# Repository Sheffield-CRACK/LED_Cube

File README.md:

# Trackellite
Software for desktop satellite tracking toy. 
Will query for TLE files daily, and produce a grid of how many satellites are where in real time. This uses an arduino and a series of SIPO shift registers to drive the actual cube. The python script `send_cube.py` contains a function, `conv2byte_vect`, which converts a numpy array (or list) to something that can be transmitted to the arduino. Something like this:

```python
# Start the serial connection
ser = serial.Serial('/dev/cu.wchusbserial72', 9600, timeout=.1)
print("Waiting for Arduino to start...")
time.sleep(2)
print("\n\n\nReady to start transmitting!")

# Bouncing Box
di = 1
i = 1
while True:
    if i == 6 or i == 0:
        di = -di
    i += di

    temp_data = np.array(data, copy=True)
    temp_data[i:i+2, i:i+2, i:i+2] = 1

    writeable_data = conv2byte_vect(temp_data)
    ser.write(writeable_data)

    time.sleep(0.1)

ser.close()
```

## TLE, and the basics of the Raspberry Pi's job
This is how satellite/orbital junk ephemerides are reported. It's basically just the position of the thing at two moments in time, then you extrapolate out from there. I'm using ported NASA code to do this - if it's good enough for NASA it's good enough for me, and I cant be arsed to write the code for that. They're somehow still using a system built to work with punchcards? Fortran users must feel vindicated.

Once a day, the full list of TLE files from [here](https://celestrak.com/NORAD/elements/) is downloaded, and each is checked to see if it passes overhead to the user. If it does, the pi puts it in its pocket, but if it doesn't it gets chucked away. Then, the pi starts constantly checking what's overhead and generating a grid, with the number of objects in each cell. The grid corresponds to the volume of space above the user. The plan is to then use this to light up the grid, corresponding to how the space junk is positioned above the user.

# Checklist:
- [DONE] [SLOW, DONT USE] Query N2YO for satellites
- [DONE] Compute my own satellite locations
- [DONE] Figure out how to plug the grid into LED matrix
  - LED matrix, c.f. [here](https://www.instructables.com/id/Led-Cube-8x8x8/)?
- [DONE] Get the software running on a raspberry pi (3B+? or will a zero work?)
- Breadboard a prototype LED matrix [DONE] and control it [TODO]
  - This needs to be done differently. I was going to do it straight off the pi, but thinking about it, it'd be better to have one (or several) arudinos handle the LEDs, so that the pi can focus on the satellites. An arduino MEGA has like, 56 GPIO pins or something, so one of those could easily handle a 4x5x5 grid (4 + 25 pins needed). Slap some transistors on that and we'd be good to go I think, though I'd probably want a breadboard hat for the arduino, vs *learning how to make a PCB(!!)* and getting that manufactured. And there's no way I'm doing this with loose wires.
- [DONE] Wire together a 3D grid of LEDs
  - I bought some stainless steel wire to use as conductor and scaffold - but solder doesn't stick to it >:(
  - I need something else. Bare steel wire maybe? Or use the scaffold and wrap a current carrier around it? [This worked]
- [DONE] Control the cube from python, through the arduino driver.
- [lol] Make a nice case
- Add a screen? Links to satellites on web trackers for more info?

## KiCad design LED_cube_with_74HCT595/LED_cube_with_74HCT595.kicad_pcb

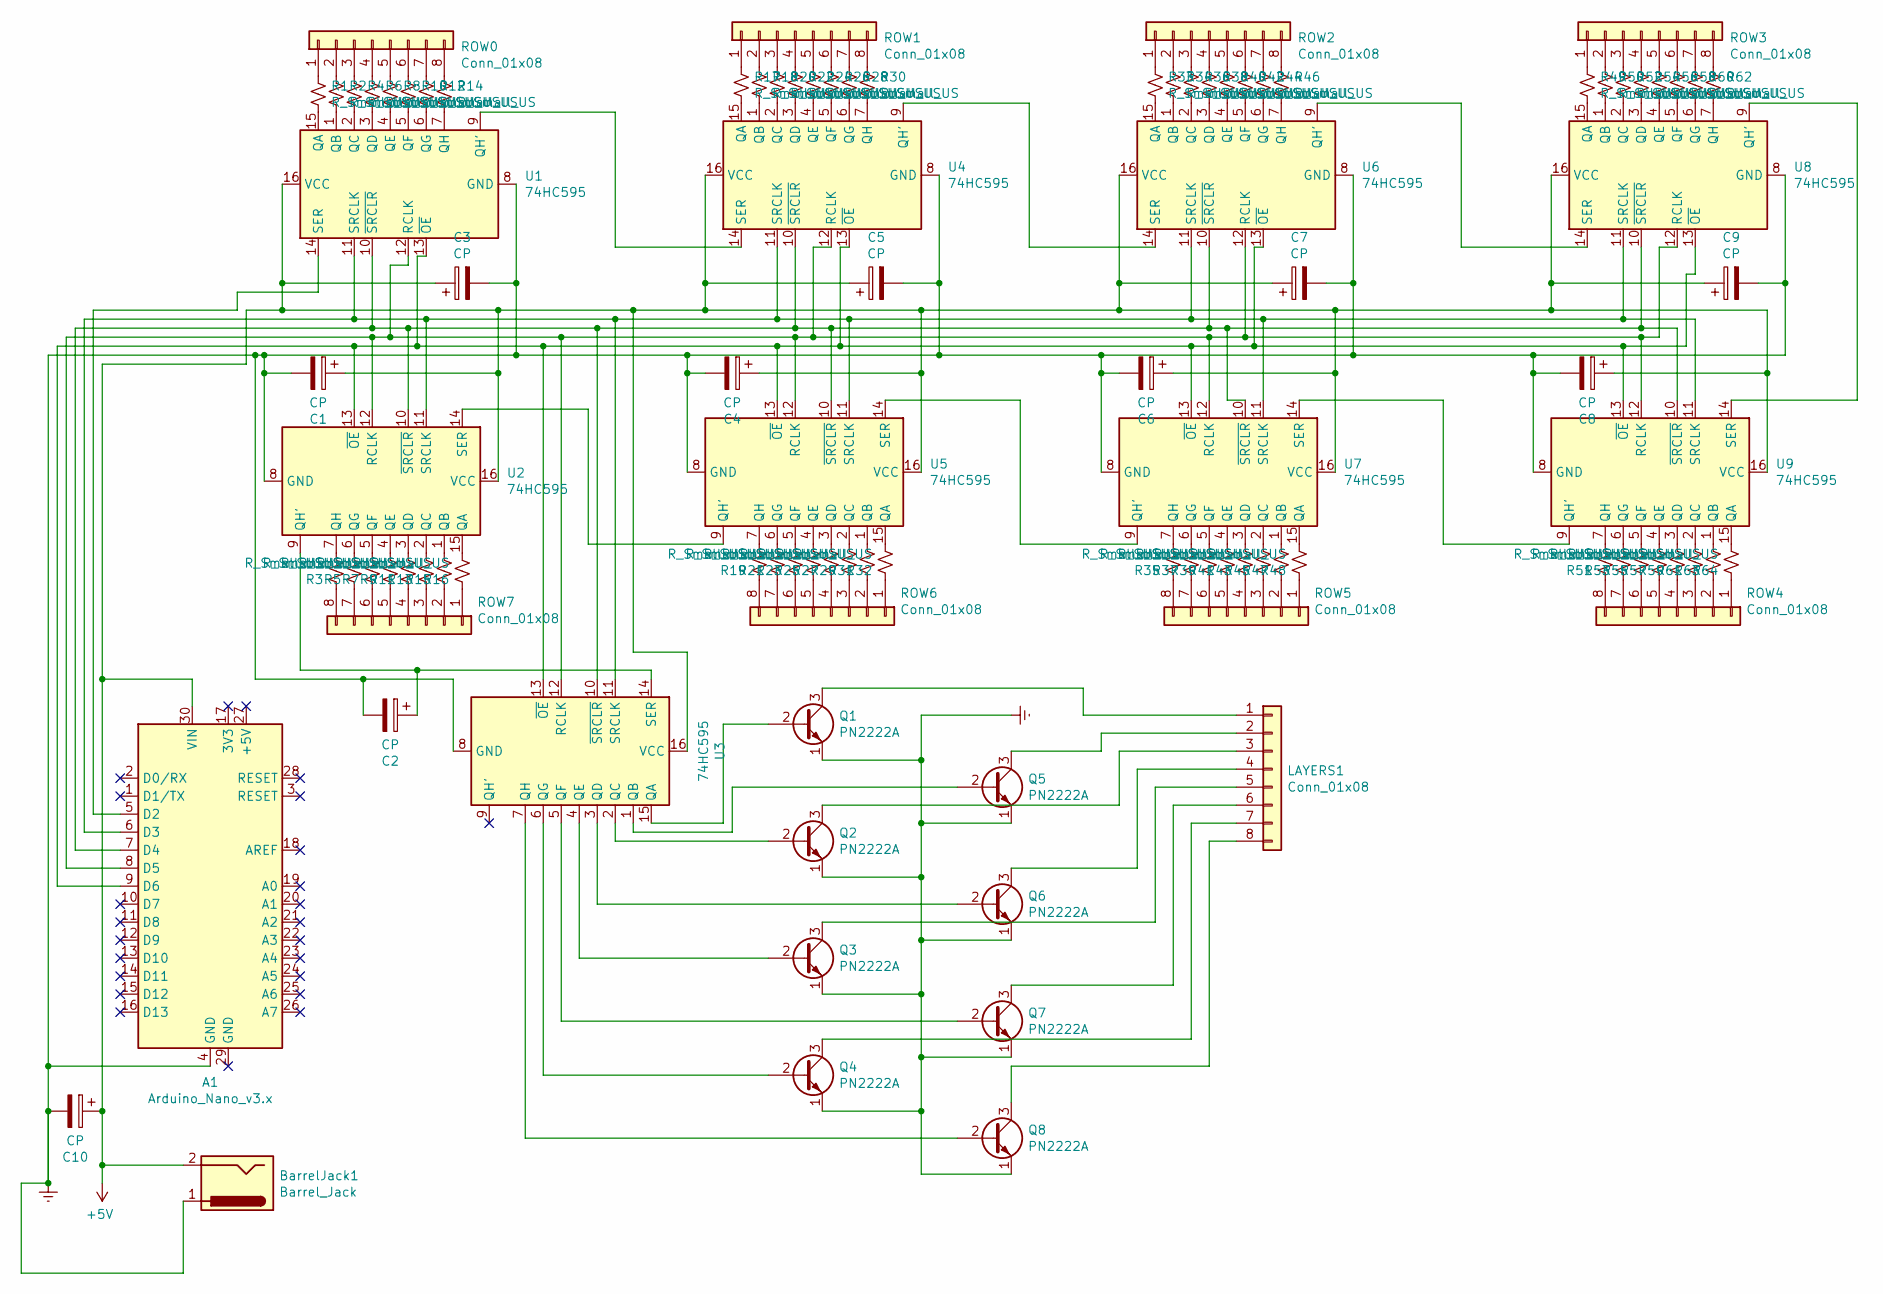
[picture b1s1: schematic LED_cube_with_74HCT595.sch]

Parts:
A1: Arduino_Nano_v3.x; Arduino_Nano
BarrelJack1: Barrel_Jack; BarrelJack_CUI_PJ-102AH_Horizontal
C1, C2, C3, C4, C5, C6, C7, C8, C9, C10: CP; CP_Radial_D4.0mm_P2.00mm
LAYERS1: Conn_01x08; PinHeader_1x08_P2.00mm_Vertical
Q1, Q2, Q3, Q4, Q5, Q6, Q7, Q8: PN2222A; TO-92_Inline
R1, R2, R3, R4, R5, R6, R7, R8, R9, R10, R11, R12, R13, R14, R15, R16, R17, R18, R19, R20, R21, R22, R23, R24, R25, R26, R27, R28, R29, R30, R31, R32, R33, R34, R35, R36, R37, R38, R39, R40, R41, R42, R43, R44, R45, R46, R47, R48, R49, R50, R51, R52, R53, R54, R55, R56, R57, R58, R59, R60, R61, R62, R63, R64: R_Small_US; R_Axial_DIN0204_L3.6mm_D1.6mm_P5.08mm_Horizontal
ROW0, ROW1, ROW2, ROW3, ROW4, ROW5, ROW6, ROW7: Conn_01x08; PinHeader_1x08_P2.00mm_Vertical
U1, U2, U3, U4, U5, U6, U7, U8, U9: 74HC595; DIP-16_W7.62mm_LongPads

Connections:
+5V: A1.30 (VIN), BarrelJack1.2, C1.1, C3.1, C4.1, C5.1, C6.1, C7.1, C8.1, C9.1, C10.1, U1.16 (VCC), U2.16 (VCC), U3.16 (VCC), U4.16 (VCC), U5.16 (VCC), U6.16 (VCC), U7.16 (VCC), U8.16 (VCC), U9.16 (VCC)
Earth: A1.4 (GND), BarrelJack1.1, C1.2, C2.2, C3.2, C4.2, C5.2, C6.2, C7.2, C8.2, C9.2, C10.2, Q1.1 (E), Q2.1 (E), Q3.1 (E), Q4.1 (E), Q5.1 (E), Q6.1 (E), Q7.1 (E), Q8.1 (E), U1.8 (GND), U2.8 (GND), U3.8 (GND), U4.8 (GND), U5.8 (GND), U6.8 (GND), U7.8 (GND), U8.8 (GND), U9.8 (GND)
unnamed: A1.5 (D2), U1.14 (SER)
unnamed: A1.6 (D3), U1.11 (SRCLK), U2.11 (SRCLK), U3.11 (SRCLK), U4.11 (SRCLK), U5.11 (SRCLK), U6.11 (SRCLK), U7.11 (SRCLK), U8.11 (SRCLK), U9.11 (SRCLK)
unnamed: A1.7 (D4), U1.10 (~SRCLR), U2.10 (~SRCLR), U3.10 (~SRCLR), U4.10 (~SRCLR), U5.10 (~SRCLR), U6.10 (~SRCLR), U7.10 (~SRCLR), U8.10 (~SRCLR), U9.10 (~SRCLR)
unnamed: A1.8 (D5), U1.12 (RCLK), U2.12 (RCLK), U3.12 (RCLK), U4.12 (RCLK), U5.12 (RCLK), U6.12 (RCLK), U7.12 (RCLK), U8.12 (RCLK), U9.12 (RCLK)
unnamed: A1.9 (D6), U1.13 (~OE), U2.13 (~OE), U3.13 (~OE), U4.13 (~OE), U5.13 (~OE), U6.13 (~OE), U7.13 (~OE), U8.13 (~OE), U9.13 (~OE)
unnamed: C2.1, U2.9 (QH'), U3.14 (SER)
unnamed: LAYERS1.1, Q1.3 (C)
unnamed: LAYERS1.2, Q5.3 (C)
unnamed: LAYERS1.3, Q2.3 (C)
unnamed: LAYERS1.4, Q6.3 (C)
unnamed: LAYERS1.5, Q3.3 (C)
unnamed: LAYERS1.6, Q7.3 (C)
unnamed: LAYERS1.7, Q4.3 (C)
unnamed: LAYERS1.8, Q8.3 (C)
unnamed: Q1.2 (B), U3.15 (QA)
unnamed: Q2.2 (B), U3.2 (QC)
unnamed: Q3.2 (B), U3.4 (QE)
unnamed: Q4.2 (B), U3.6 (QG)
unnamed: Q5.2 (B), U3.1 (QB)
unnamed: Q6.2 (B), U3.3 (QD)
unnamed: Q7.2 (B), U3.5 (QF)
unnamed: Q8.2 (B), U3.7 (QH)
unnamed: R1.1, ROW0.1
unnamed: R1.2, U1.15 (QA)
unnamed: R2.1, ROW0.2
unnamed: R2.2, U1.1 (QB)
unnamed: R3.1, ROW7.8
unnamed: R3.2, U2.7 (QH)
unnamed: R4.1, ROW0.3
unnamed: R4.2, U1.2 (QC)
unnamed: R5.1, ROW7.7
unnamed: R5.2, U2.6 (QG)
unnamed: R6.1, ROW0.4
unnamed: R6.2, U1.3 (QD)
unnamed: R7.1, ROW7.6
unnamed: R7.2, U2.5 (QF)
unnamed: R8.1, ROW0.5
unnamed: R8.2, U1.4 (QE)
unnamed: R9.1, ROW7.5
unnamed: R9.2, U2.4 (QE)
unnamed: R10.1, ROW0.6
unnamed: R10.2, U1.5 (QF)
unnamed: R11.1, ROW7.4
unnamed: R11.2, U2.3 (QD)
unnamed: R12.1, ROW0.7
unnamed: R12.2, U1.6 (QG)
unnamed: R13.1, ROW7.3
unnamed: R13.2, U2.2 (QC)
unnamed: R14.1, ROW0.8
unnamed: R14.2, U1.7 (QH)
unnamed: R15.1, ROW7.2
unnamed: R15.2, U2.1 (QB)
unnamed: R16.1, ROW7.1
unnamed: R16.2, U2.15 (QA)
unnamed: R17.1, ROW1.1
unnamed: R17.2, U4.15 (QA)
unnamed: R18.1, ROW1.2
unnamed: R18.2, U4.1 (QB)
unnamed: R19.1, ROW6.8
unnamed: R19.2, U5.7 (QH)
unnamed: R20.1, ROW1.3
unnamed: R20.2, U4.2 (QC)
unnamed: R21.1, ROW6.7
unnamed: R21.2, U5.6 (QG)
unnamed: R22.1, ROW1.4
unnamed: R22.2, U4.3 (QD)
unnamed: R23.1, ROW6.6
unnamed: R23.2, U5.5 (QF)
unnamed: R24.1, ROW1.5
unnamed: R24.2, U4.4 (QE)
unnamed: R25.1, ROW6.5
unnamed: R25.2, U5.4 (QE)
unnamed: R26.1, ROW1.6
unnamed: R26.2, U4.5 (QF)
unnamed: R27.1, ROW6.4
unnamed: R27.2, U5.3 (QD)
unnamed: R28.1, ROW1.7
unnamed: R28.2, U4.6 (QG)
unnamed: R29.1, ROW6.3
unnamed: R29.2, U5.2 (QC)
unnamed: R30.1, ROW1.8
unnamed: R30.2, U4.7 (QH)
unnamed: R31.1, ROW6.2
unnamed: R31.2, U5.1 (QB)
unnamed: R32.1, ROW6.1
unnamed: R32.2, U5.15 (QA)
unnamed: R33.1, ROW2.1
unnamed: R33.2, U6.15 (QA)
unnamed: R34.1, ROW2.2
unnamed: R34.2, U6.1 (QB)
unnamed: R35.1, ROW5.8
unnamed: R35.2, U7.7 (QH)
unnamed: R36.1, ROW2.3
unnamed: R36.2, U6.2 (QC)
unnamed: R37.1, ROW5.7
unnamed: R37.2, U7.6 (QG)
unnamed: R38.1, ROW2.4
unnamed: R38.2, U6.3 (QD)
unnamed: R39.1, ROW5.6
unnamed: R39.2, U7.5 (QF)
unnamed: R40.1, ROW2.5
unnamed: R40.2, U6.4 (QE)
unnamed: R41.1, ROW5.5
unnamed: R41.2, U7.4 (QE)
unnamed: R42.1, ROW2.6
unnamed: R42.2, U6.5 (QF)
unnamed: R43.1, ROW5.4
unnamed: R43.2, U7.3 (QD)
unnamed: R44.1, ROW2.7
unnamed: R44.2, U6.6 (QG)
unnamed: R45.1, ROW5.3
unnamed: R45.2, U7.2 (QC)
unnamed: R46.1, ROW2.8
unnamed: R46.2, U6.7 (QH)
unnamed: R47.1, ROW5.2
unnamed: R47.2, U7.1 (QB)
unnamed: R48.1, ROW5.1
unnamed: R48.2, U7.15 (QA)
unnamed: R49.1, ROW3.1
unnamed: R49.2, U8.15 (QA)
unnamed: R50.1, ROW3.2
unnamed: R50.2, U8.1 (QB)
unnamed: R51.1, ROW4.8
unnamed: R51.2, U9.7 (QH)
unnamed: R52.1, ROW3.3
unnamed: R52.2, U8.2 (QC)
unnamed: R53.1, ROW4.7
unnamed: R53.2, U9.6 (QG)
unnamed: R54.1, ROW3.4
unnamed: R54.2, U8.3 (QD)
unnamed: R55.1, ROW4.6
unnamed: R55.2, U9.5 (QF)
unnamed: R56.1, ROW3.5
unnamed: R56.2, U8.4 (QE)
unnamed: R57.1, ROW4.5
unnamed: R57.2, U9.4 (QE)
unnamed: R58.1, ROW3.6
unnamed: R58.2, U8.5 (QF)
unnamed: R59.1, ROW4.4
unnamed: R59.2, U9.3 (QD)
unnamed: R60.1, ROW3.7
unnamed: R60.2, U8.6 (QG)
unnamed: R61.1, ROW4.3
unnamed: R61.2, U9.2 (QC)
unnamed: R62.1, ROW3.8
unnamed: R62.2, U8.7 (QH)
unnamed: R63.1, ROW4.2
unnamed: R63.2, U9.1 (QB)
unnamed: R64.1, ROW4.1
unnamed: R64.2, U9.15 (QA)
unnamed: U1.9 (QH'), U4.14 (SER)
unnamed: U2.14 (SER), U5.9 (QH')
unnamed: U4.9 (QH'), U6.14 (SER)
unnamed: U5.14 (SER), U7.9 (QH')
unnamed: U6.9 (QH'), U8.14 (SER)
unnamed: U7.14 (SER), U9.9 (QH')
unnamed: U8.9 (QH'), U9.14 (SER)

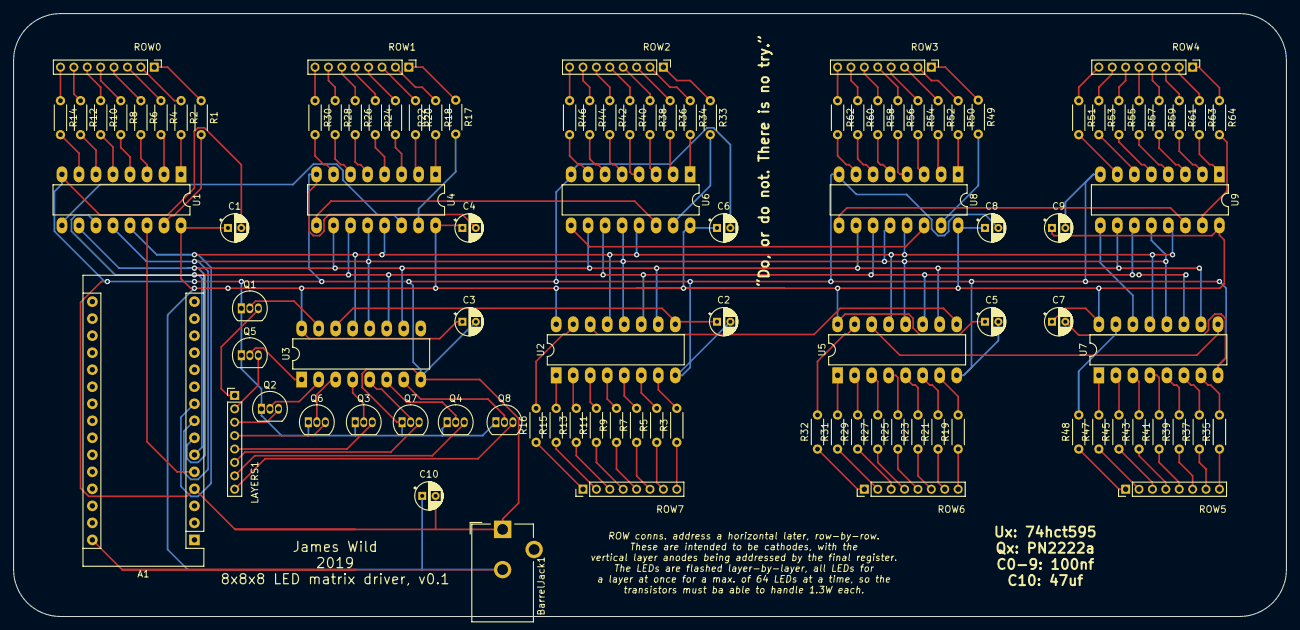
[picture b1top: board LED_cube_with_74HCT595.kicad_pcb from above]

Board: 2 copper layers, 190.0 x 90.0 mm, 102 parts (0 on the bottom side), 159 nets.

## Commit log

2019-07-30 Initial upload
2019-07-30 Added gitignore
2019-07-30 Removed chaff
2019-07-31 Added grid constructor
2019-07-31 First look at LED logic. Upload a shopping list
2019-07-31 Updated spreadsheet
2019-07-31 Dont upload the temporary files!
2019-08-03 Began to impliment the LED handling software
2019-08-03 Dumb error
2019-08-04 Moved LED handler to class
2019-08-04 Making decisions about how to deal out the pin numbers
2019-08-04 Added a close method
2019-08-05 Threaded the LED handler
2019-08-05 Minor commit
2019-08-09 Made the unusable pins 0 and 1 optionally skippable
2019-09-09 Set theme jekyll-theme-slate
2019-11-19 Shift register begun
2019-11-19 Slow down
2019-11-19 DELETEME
2020-01-16 Updated to use shift registers
2020-01-16 Ignore spreadsheets
2020-01-16 Made send_cube importable
2020-01-16 Syntax bug
2020-01-21 Encapsulated the cube sending and connecting
2020-01-21 Ignore my shite
2020-01-21 Removed shite
2020-01-21 Ignore shite
2020-01-21 Uploaded PCB design. Uploaded rain animation
2020-01-21 Tried to make the connect_cube detect the arduino automagically
2020-01-21 Updated TLE_sats to use the cube
2020-01-21 Removed bad code
2020-01-22 Fixed non-working connect_cube code
2020-01-22 Minor change
